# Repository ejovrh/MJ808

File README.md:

# keywords:

Magicshine, bicycle front light, MJ808, MJ-808, MJ818, MJ-818, bicycle rear light, CAN bus

BRANCH GW

# 0. this all is still under heavy development
front and rear lamps do work together and can be used on a bike.
logic unit and auxiliary devices are still WIP.

# 1. abstract:
this undertaking originated as an attempt to redesign the MJ808/MJ818 lights by:
- designing a custom PCB w. driver/controller ICs,
- writing firmware for a stm32 microcontroller,
- encapsulating the above in MJ808's/MJ818's original housing,
- combining:
 - the rear light (MJ818), 
 - the front light (MJ808) and 
 - a control unit into an interconnected smart bicycle light system.
 - developing further auxiliary devices which extend functionality of the lights.

# 2. light system topology (in ascii art)
**==** and **||** denote the CAN bus, power lines are omitted.

## 2.1 - current working setup
front and rear lights are interconnected via the CAN bus; the front light activates the rear light via commands transmitted over CAN.

	(front light) - (rear light)
	------------------------------------------------
	(mj808) ======  (mj818)
	
## 2.2 - WIP setup
front and rear lights are extended in their functionality by other auxiliary devices interconnected via the CAN bus
	
	(front light) - (control unit) - (rear light)
	------------------------------------------------
	(mj808) ====== (control unit)  ====== (mj818)
                      ||		||
                      ||		||		
                      ||	(future device(s))
                    (dynamo)

# 3. description of the original light
google [magicshine mj-818](https://www.google.com/search?q=magicshine+mj-818) / [magicshine mj-808](https://www.google.com/search?q=magicshine+mj-808) for an idea what the lights are and look like.
	
these are decent made-in-china bicycle lights operated off a 2S2P Li-Lion battery pack.

their functionality, apart from producing light, sucks.

# 4. motivation for development
light operating mode selection and high power consumption on the original lights is what i would like to have different.
	
the only reasonable way to achieve this is to start from scratch.

# 5. required software for DIY building
- eagle for PCB layout & schematics,
- STM32CubeIDE for the code,
- one STLink or similar,
- some cheapo arduino/stm-based CAN capable dev. board for quick and dirty CAN testing
- SMD soldering equipment and skills,
- parts.

# 6. repo structure
- /datasheets/*/: contains what the name suggests,
- /dwg/: AutoCAD drawings & STLs of various sub-components,
- /eagle designs/: contains subfolders with eagle designs (.brd, .sch & BOMs) of various sub-components:
	- mj808/: the front light,
	- mj818/: the rear light,
	- mj828/: a small handlebar mounted UI (nothing fancy), WIP,
	- mj838/ (aka. Čos): a dynamo thing, WIP,
	- mjfoo/: a development board based on the mj8x8 infractructure,
	- branch-dependant: whatever stuff is in the particular branch.
- /mj8x8/: C source code for everything, to be used with STM32CubeIDE
- /saleae/: HLA for the logic analyzer
	
# 7. hardware
look in [/datasheets/](https://github.com/ejovrh/MJ808/tree/master/datasheets) for a BOM.

core components:
- 4-layer PCB manufactured via [OSH Park](https://oshpark.com/),
- [STM32F042G6U6](https://www.st.com/en/microcontrollers-microprocessors/stm32f042g6.html) microcontroller, 
- [TCAN334](https://www.ti.com/product/TCAN334) 3.3V CAN transciever,
- [MAX16819](https://www.maximintegrated.com/en/products/power/led-drivers/MAX16819.html) & [MAX16820](https://www.maximintegrated.com/en/products/power/led-drivers/MAX16820.html) LED drivers,
- [LDK320](https://www.st.com/en/power-management/ldk320.html) 5V LDO,
- 0402 passives and
- Cree [XM-L](https://www.cree.com/led-components/products/xlamp-leds-discrete/xlamp-xm-l) and [XP-E](https://www.cree.com/led-components/products/xlamp-leds-discrete/xlamp-xp-e) high power LEDs.

when chosing components the primary criterium was size, since everything needed to fit into existing housings.
maximizing light output to the extreme was not a design factor.

# 8. software
## 8.1 general overview
the language of choice is C, written in an object-oriented fashion:
- it uses HAL. (don't like it?  -> go away.),
- common core components translate into an [abstract base class](https://github.com/ejovrh/MJ808/tree/master/MJ808/MJ808/mj8x8) (implemented via C-structs), 
- concrete implementations (e.g. [mj808](https://github.com/ejovrh/MJ808/tree/master/MJ808/MJ808/mj808) ) translate into derived classes (again C-structs),
- methods are generally implemented via function pointers ([e.g. CAN driver message operations](https://github.com/ejovrh/MJ808/blob/master/MJ808/MJ808/mj8x8/mcp2515.h)),
- behaviour is sometimes achieved with [OO interfaces](https://github.com/ejovrh/MJ808/tree/master/MJ808/MJ808/led), 
- polymorphism is implemented manually via constructors ([ctor in mj808_t](https://github.com/ejovrh/MJ808/blob/master/MJ808/MJ808/mj808/mj808.c)) and
- information is hidden by nesting C-structs and placing them into either [.c](https://github.com/ejovrh/MJ808/blob/master/MJ808/MJ808/mj808/mj808.c) or [.h](https://github.com/ejovrh/MJ808/blob/master/MJ808/MJ808/mj808/mj808.h) files.

due to memory limitations there are only hints of SOLID and design patterns to be found.

code is commented in a somewhat reasonable manner.

## 8.2 detailed description
TODO

## 8.2.1 mj808 - front light

## 8.2.2 mj818 - rear light

## 8.2.3 mj828 - UI

## 8.2.4 mjfoo - development board

## 8.2.5 mj838 - power controller

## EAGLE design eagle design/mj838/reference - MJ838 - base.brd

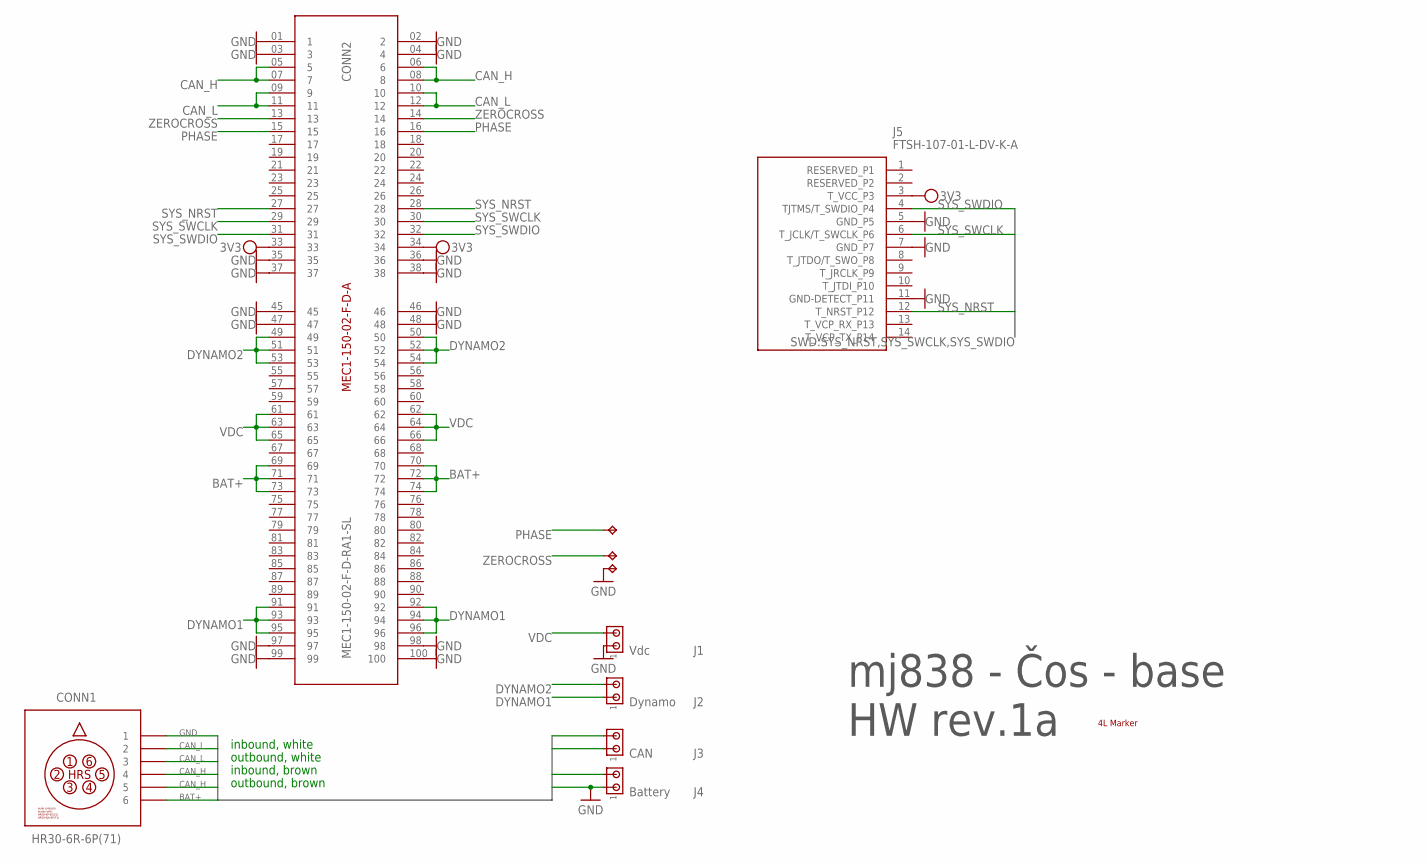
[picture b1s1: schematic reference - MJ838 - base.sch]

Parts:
CONN2: MEC1-150-02-F-D-RA1-SL; SAMTEC_MEC1-150-2-F-D-RA1
J1: Vdc; 10X02MTA
J2: Dynamo; 10X02MTA
J3: CAN; 10X02MTA
J4: Battery; 10X02MTA
J5: FTSH-107-01-L-DV-K-A; FTSH10701LDVKA
MARKER2: 4 Layer marker; 4L
TP1, TP2, TP3: TPPAD1-13; P1-13

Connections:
3V3: CONN2.33, CONN2.34, J5.3 (T_VCC_P3)
BAT+: CONN2.69, CONN2.70, CONN2.71, CONN2.72, CONN2.73, CONN2.74, J4.2
CAN_H: CONN2.05 (5), CONN2.06 (6), CONN2.07 (7), CONN2.08 (8), J3.2
CAN_L: CONN2.09 (9), CONN2.10, CONN2.11, CONN2.12, J3.1
DYNAMO1: CONN2.91, CONN2.92, CONN2.93, CONN2.94, CONN2.95, CONN2.96, J2.1
DYNAMO2: CONN2.49, CONN2.50, CONN2.51, CONN2.52, CONN2.53, CONN2.54, J2.2
GND: CONN2.01 (1), CONN2.02 (2), CONN2.03 (3), CONN2.04 (4), CONN2.35, CONN2.36, CONN2.37, CONN2.38, CONN2.45, CONN2.46, CONN2.47, CONN2.48, CONN2.97, CONN2.98, CONN2.99, CONN2.100, J1.1, J4.1, J5.5 (GND_P5), J5.7 (GND_P7), J5.11 (GND-DETECT_P11), TP1.TP
PHASE: CONN2.15, CONN2.16, TP3.TP
SYS_NRST: CONN2.27, CONN2.28, J5.12 (T_NRST_P12)
SYS_SWCLK: CONN2.29, CONN2.30, J5.6 (T_JCLK/T_SWCLK_P6)
SYS_SWDIO: CONN2.31, CONN2.32, J5.4 (TJTMS/T_SWDIO_P4)
VDC: CONN2.61, CONN2.62, CONN2.63, CONN2.64, CONN2.65, CONN2.66, J1.2
ZEROCROSS: CONN2.13, CONN2.14, TP2.TP

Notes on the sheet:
inbound, white
inbound, brown
outbound, white
outbound, brown
mj838 - Čos - base HW rev.1a

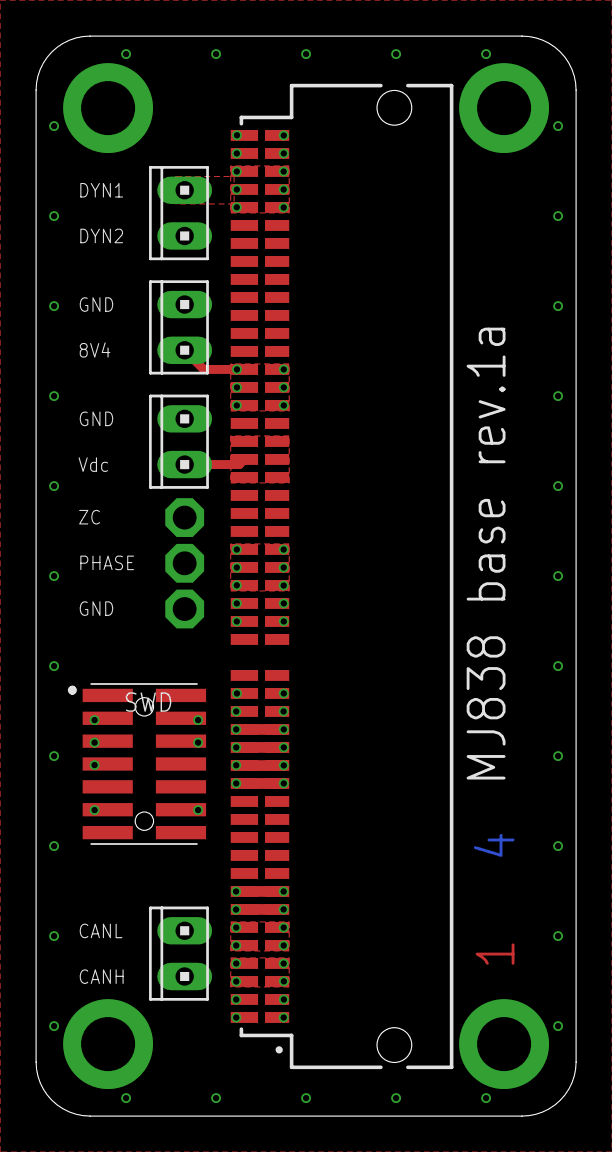
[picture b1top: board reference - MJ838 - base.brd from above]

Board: 4 copper layers, 30.0 x 60.0 mm, 10 parts (0 on the bottom side), 13 nets.

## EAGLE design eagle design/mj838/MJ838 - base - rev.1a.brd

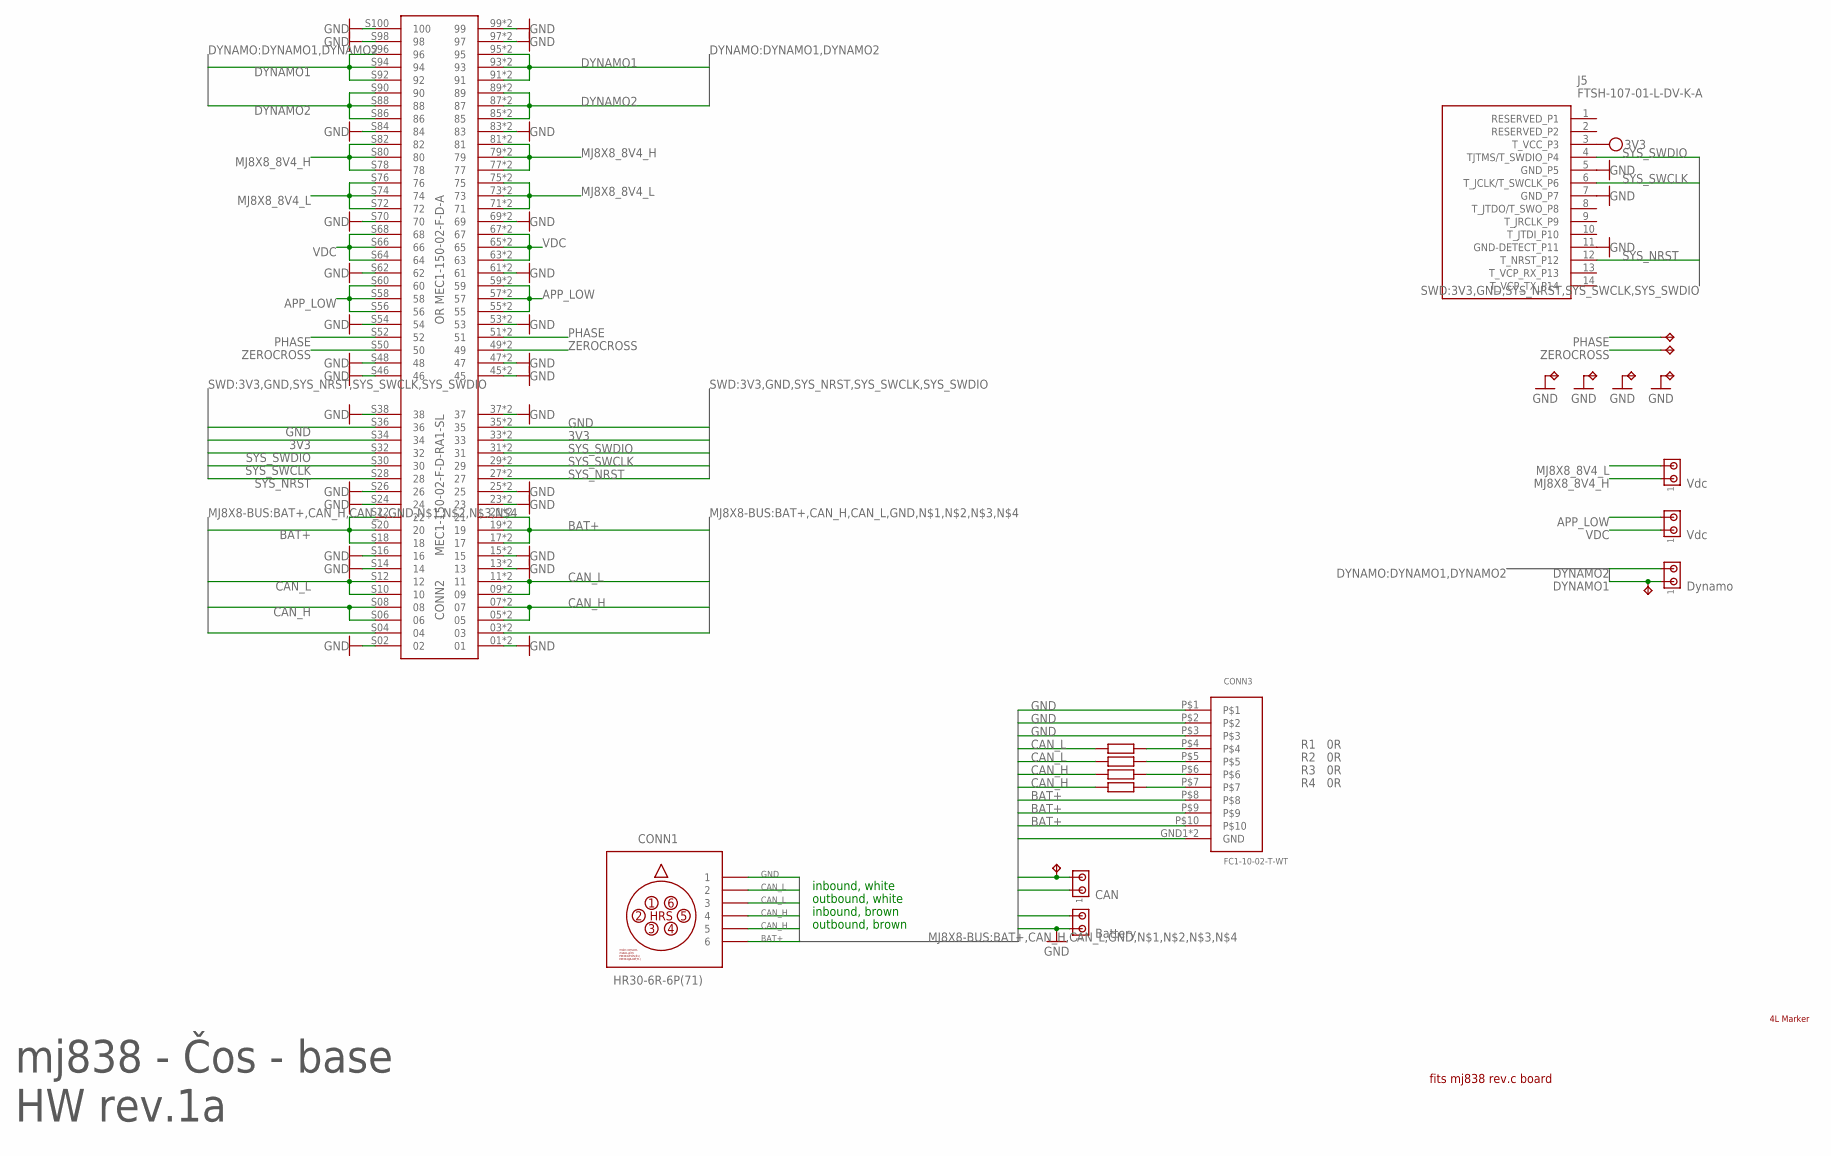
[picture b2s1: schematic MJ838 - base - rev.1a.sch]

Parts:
CONN2: MEC1-150-02-F-D-RA1-SL; MEC1-150-02-F-D-COMBINED
CONN3: FC1-10-02-T-WT; SMD
J2: Dynamo; 10X02MTA
J3: CAN; 10X02MTA
J4: Battery; 10X02MTA
J5: FTSH-107-01-L-DV-K-A; FTSH10701LDVKA
J6, J7: Vdc; 10X02MTA
MARKER2: 4 Layer marker; 4L
R1, R2, R3, R4: 0R; R0402
TP1, TP2, TP3, TP4, TP5, TP6, TP8, TP9: TPPAD1-13; P1-13

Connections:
3V3: CONN2.33, CONN2.R33 (33), CONN2.S34 (34), J5.3 (T_VCC_P3)
APP_LOW: CONN2.55, CONN2.57, CONN2.59, CONN2.R55 (55), CONN2.R57 (57), CONN2.R59 (59), CONN2.S56 (56), CONN2.S58 (58), CONN2.S60 (60), J7.2
BAT+: CONN2.17, CONN2.19, CONN2.21, CONN2.R17 (17), CONN2.R19 (19), CONN2.R21 (21), CONN2.S18 (18), CONN2.S20 (20), CONN2.S22 (22), CONN3.P$8, CONN3.P$9, CONN3.P$10, J4.2
CAN_H: CONN2.05, CONN2.07, CONN2.R05 (05), CONN2.R07 (07), CONN2.S06 (06), CONN2.S08 (08), J3.2, R3.1, R4.1, TP6.TP
CAN_L: CONN2.09, CONN2.11, CONN2.R09 (09), CONN2.R11 (11), CONN2.S10 (10), CONN2.S12 (12), J3.1, R1.1, R2.1
DYNAMO1: CONN2.91, CONN2.93, CONN2.95, CONN2.R91 (91), CONN2.R93 (93), CONN2.R95 (95), CONN2.S92 (92), CONN2.S94 (94), CONN2.S96 (96), J2.1, TP5.TP
DYNAMO2: CONN2.85, CONN2.87, CONN2.89, CONN2.R85 (85), CONN2.R87 (87), CONN2.R89 (89), CONN2.S86 (86), CONN2.S88 (88), CONN2.S90 (90), J2.2
GND: CONN2.01, CONN2.03, CONN2.13, CONN2.15, CONN2.23, CONN2.25, CONN2.35, CONN2.37, CONN2.45, CONN2.47, CONN2.53, CONN2.61, CONN2.69, CONN2.83, CONN2.97, CONN2.99, CONN2.R01 (01), CONN2.R03 (03), CONN2.R13 (13), CONN2.R15 (15), CONN2.R23 (23), CONN2.R25 (25), CONN2.R35 (35), CONN2.R37 (37), CONN2.R45 (45), CONN2.R47 (47), CONN2.R53 (53), CONN2.R61 (61), CONN2.R69 (69), CONN2.R83 (83), CONN2.R97 (97), CONN2.R99 (99), CONN2.S02 (02), CONN2.S04 (04), CONN2.S14 (14), CONN2.S16 (16), CONN2.S24 (24), CONN2.S26 (26), CONN2.S36 (36), CONN2.S38 (38), CONN2.S46 (46), CONN2.S48 (48), CONN2.S54 (54), CONN2.S62 (62), CONN2.S70 (70), CONN2.S84 (84), CONN2.S98 (98), CONN2.S100 (100), CONN3.GND1 (GND), CONN3.GND2 (GND), CONN3.P$1, CONN3.P$2, CONN3.P$3, J4.1, J5.5 (GND_P5), J5.7 (GND_P7), J5.11 (GND-DETECT_P11), TP1.TP, TP4.TP, TP8.TP, TP9.TP
MJ8X8_8V4_H: CONN2.77, CONN2.79, CONN2.81, CONN2.R77 (77), CONN2.R79 (79), CONN2.R81 (81), CONN2.S78 (78), CONN2.S80 (80), CONN2.S82 (82), J6.1
MJ8X8_8V4_L: CONN2.71, CONN2.73, CONN2.75, CONN2.R71 (71), CONN2.R73 (73), CONN2.R75 (75), CONN2.S72 (72), CONN2.S74 (74), CONN2.S76 (76), J6.2
unnamed: CONN3.P$4, R1.2
unnamed: CONN3.P$5, R2.2
unnamed: CONN3.P$6, R3.2
unnamed: CONN3.P$7, R4.2
PHASE: CONN2.51, CONN2.R51 (51), CONN2.S52 (52), TP3.TP
SYS_NRST: CONN2.27, CONN2.R27 (27), CONN2.S28 (28), J5.12 (T_NRST_P12)
SYS_SWCLK: CONN2.29, CONN2.R29 (29), CONN2.S30 (30), J5.6 (T_JCLK/T_SWCLK_P6)
SYS_SWDIO: CONN2.31, CONN2.R31 (31), CONN2.S32 (32), J5.4 (TJTMS/T_SWDIO_P4)
VDC: CONN2.63, CONN2.65, CONN2.67, CONN2.R63 (63), CONN2.R65 (65), CONN2.R67 (67), CONN2.S64 (64), CONN2.S66 (66), CONN2.S68 (68), J7.1
ZEROCROSS: CONN2.49, CONN2.R49 (49), CONN2.S50 (50), TP2.TP

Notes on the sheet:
inbound, white
inbound, brown
outbound, white
outbound, brown
mj838 - Čos - base HW rev.1a
fits mj838 rev.c board
OR MEC1-150-02-F-D-A

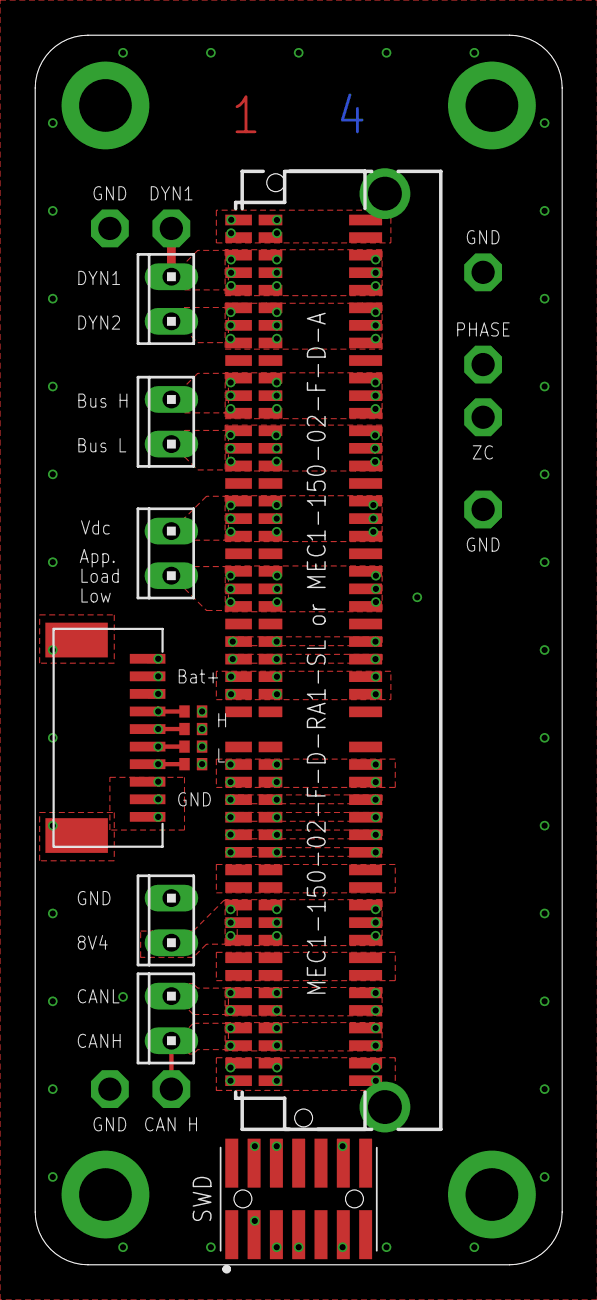
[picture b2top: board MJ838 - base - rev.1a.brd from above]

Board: 4 copper layers, 30.0 x 70.0 mm, 21 parts (0 on the bottom side), 20 nets.

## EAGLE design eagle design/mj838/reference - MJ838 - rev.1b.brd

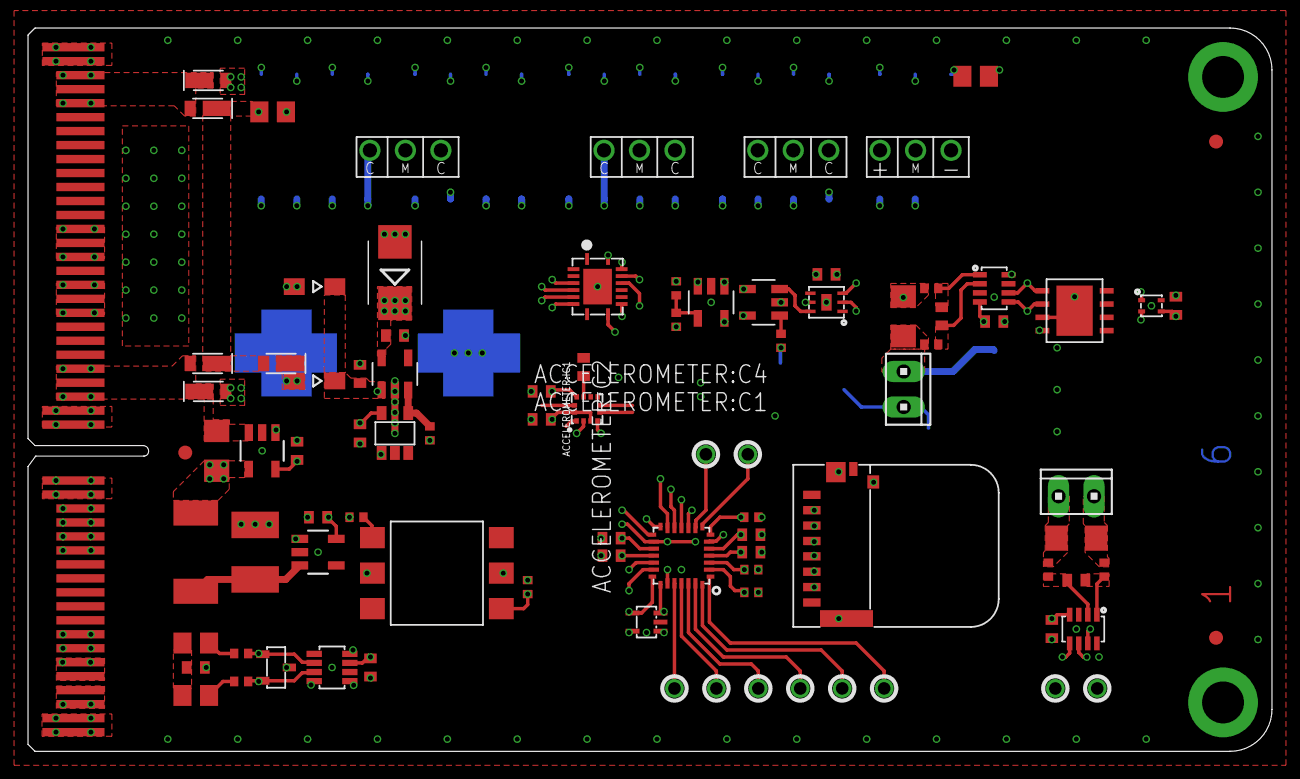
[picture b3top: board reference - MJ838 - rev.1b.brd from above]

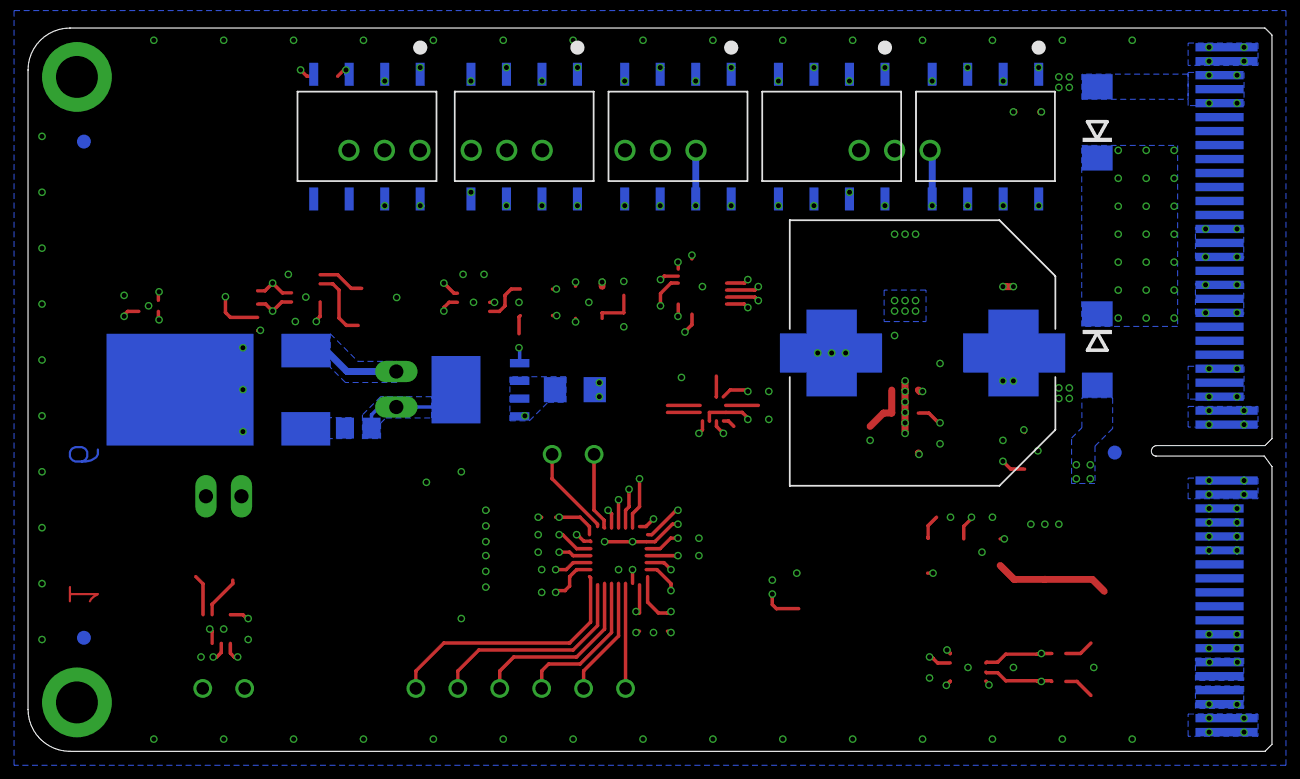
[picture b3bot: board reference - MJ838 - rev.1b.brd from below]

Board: 6 copper layers, 89.0 x 51.8 mm, 107 parts (16 on the bottom side), 76 nets.

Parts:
12R_OHMIC_LOAD:C1: 0.1uF / 10V; C0402
12R_OHMIC_LOAD:IC1: DAC121C081CISD/NOPB; WSON-6
12R_OHMIC_LOAD:IC2, 12R_OHMIC_LOAD:IC4: AD8515ARTZ-REEL7; SOT-23-5
12R_OHMIC_LOAD:IC3: PH2925U,115; SOT669
12R_OHMIC_LOAD:J3: Application; 10X02MTA
12R_OHMIC_LOAD:R1: 3k; R0402
12R_OHMIC_LOAD:R2: 0.1R / 0.5W - LVK12R100CER; R1206
12R_OHMIC_LOAD:R3: 1k; R0402
12R_OHMIC_LOAD:R4: 27k; R0402
12R_OHMIC_LOAD:R5: 12R, 20W, AP725 12R F; TO-263-2
12R_OHMIC_LOAD:R6: 0; R0805
ACCELEROMETER:C1: 0.1uF / 10V; C0402
ACCELEROMETER:C2: 0.2uF / 10V; C0402
ACCELEROMETER:C4: 0.11uF / 10V; C0402
ACCELEROMETER:IC1: ADXL367BCCZ-RL7; LGA-12
CAN_INFRA:C1: 47nF / 10V; C0402
CAN_INFRA:C5: 0.1uF / 10V; C0402
CAN_INFRA:IC1: TCAN334GDCNT; SOT23-8
CAN_INFRA:IC2: SZNUP2105LT1G; SOT-23-3
CAN_INFRA:R1, CAN_INFRA:R2: 60R, 0.5W; R0805
CAN_INFRA:R3, CAN_INFRA:R4: 0; R0402
CONN1: MEC1-150-02-F-D-RA1-SL; SMD
D1: SMLVT3V3; SMB
FE-RAM:IC1: FM24CL64B-DGTR; DFN8
FID1, FID2, FID3, FID4, FID5, FID6: n/a; FIDUCIAL_1MM
HUMIDITY_SENSOR:C5: 0.1uF / 10V; C0402
HUMIDITY_SENSOR:IC1: SHT40-AD1F-R2; SMD
IC1: ESDALC6V1W5; SOT323-5
INA1:C1, INA219:C1: 0.1uF / 10V; C0402
INA1:C2, INA219:C2: ???; C0402
INA1:IC3, INA219:IC3: INA219BIDCNT; SOT-23-8
INA1:R3, INA1:R5, INA219:R3, INA219:R5: ???; R0402
INA1:R4, INA219:R4: 0.1R / 0.5W - LVK12R100CER; R1206
J1: sense 1; 10X02MTA
MARKER1: 6 layer; 6L
RECTIFIER:3V3:C1, RECTIFIER:3V3:C2, RECTIFIER:3V3:C7: 1uF / 10V; C0402
RECTIFIER:3V3:IC1: R3119N058A; SOT23-5
RECTIFIER:3V3:IC2: LDK320AM33R; SOT-23-5L
RECTIFIER:3V3:R1: 100k / 0.1W; R0402
RECTIFIER:D1, RECTIFIER:D2: BAT 60A E6327; SOD323-W
RECTIFIER:GRAETZ+DELON:D1, RECTIFIER:GRAETZ+DELON:D2, RECTIFIER:GRAETZ+DELON:D3, RECTIFIER:GRAETZ+DELON:D4: CUHS20S30,H3F; US2H
RECTIFIER:GRAETZ+DELON:DELON:C1: 330μF / 35V / ultralow ESR; TH-2S
RECTIFIER:GRAETZ+DELON:DELON:SSR_NO/NO3:IC1: LAA710S; SMD_DIP8
RECTIFIER:GRAETZ+DELON:IC1: TLC59208FIRGYR; VQFN16
RECTIFIER:GRAETZ+DELON:R1: 625; R0805
RECTIFIER:GRAETZ+DELON:TUNING_CAPS:C2, RECTIFIER:GRAETZ+DELON:TUNING_CAPS:C3, RECTIFIER:GRAETZ+DELON:TUNING_CAPS:C4: 1500μF / 35V / ultralow ESR; TH-2S-BACK-TO-BACK
RECTIFIER:GRAETZ+DELON:TUNING_CAPS:R2: 47k; R0805
RECTIFIER:GRAETZ+DELON:TUNING_CAPS:SSR_NO/NO1:IC1, RECTIFIER:GRAETZ+DELON:TUNING_CAPS:SSR_NO/NO2:IC1, RECTIFIER:GRAETZ+DELON:TUNING_CAPS:SSR_NO/NO3:IC1, RECTIFIER:GRAETZ+DELON:TUNING_CAPS:SSR_NO/NO4:IC1: LAA710S; SMD_DIP8
RECTIFIER:OVP:D1, RECTIFIER:OVP:D2: 19V/5W; DO214AA
RECTIFIER:PHASE_SHIFT:C1: 0.1uF / 10V; C0402
RECTIFIER:PHASE_SHIFT:IC1: LT1716CS5#TRMPBF; SOT23-5
RECTIFIER:PHASE_SHIFT:R4: 0.01R / 0.5W / 0.25%; R1206
RECTIFIER:SMOOTHING_CAP:C1: EEE-FK1E472SV; CAP_EEEFK1E472SV
RECTIFIER:SMOOTHING_CAP:D8: CUHS20S30,H3F; US2H
RECTIFIER:ZERO-CROSS_DETECTOR:C3: 0.1uF / 10V; C0402
RECTIFIER:ZERO-CROSS_DETECTOR:C8: 10nF / 100v; C1812
RECTIFIER:ZERO-CROSS_DETECTOR:IC1: 4N25-X009T; SMD-6
RECTIFIER:ZERO-CROSS_DETECTOR:IC3: LT1716CS5#TRMPBF; SOT23-5
RECTIFIER:ZERO-CROSS_DETECTOR:R1: 10k/3W; R2512
RECTIFIER:ZERO-CROSS_DETECTOR:R2: 100R; R0402
RECTIFIER:ZERO-CROSS_DETECTOR:R3: 10k; R0402
SD_CARD:IC2: 47309-2651; MICRO_SD_CONNECTOR
SD_CARD:R1: 10k; R0402
STM32F04:C1, STM32F04:C5, STM32F04:C7: 0.1uF / 10V; C0402
STM32F04:C4: 1uF / 10V; C0402
STM32F04:IC2: STM32F042G6U6; UFQFPN-28
STM32F04:R1, STM32F04:R2: 1k; R0402
TP1, TP2, TP3, TP4, TP5, TP6, TP7, TP8, TP9, TP10: CAN high; TH-0.9

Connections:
2IN+: INA1:R4.1, INA1:R5.2, J1.1
2IN-: INA1:R3.2, INA1:R4.2, J1.2
3V3: 12R_OHMIC_LOAD:C1.2, 12R_OHMIC_LOAD:IC1.5, 12R_OHMIC_LOAD:IC2.5, 12R_OHMIC_LOAD:IC4.5, ACCELEROMETER:C1.2, ACCELEROMETER:C4.2, ACCELEROMETER:IC1.3_MISO/ASEL, ACCELEROMETER:IC1.10_VS, ACCELEROMETER:IC1.12_VDDIO, CAN_INFRA:C5.1, CAN_INFRA:IC1.P$3, CONN1.33, CONN1.34, D1.C, FE-RAM:IC1.8, HUMIDITY_SENSOR:C5.1, HUMIDITY_SENSOR:IC1.VDD, INA1:C1.1, INA1:IC3.P$4, INA1:IC3.P$7, INA219:C1.1, INA219:IC3.P$4, RECTIFIER:3V3:C7.2, RECTIFIER:3V3:IC2.OUT, RECTIFIER:GRAETZ+DELON:IC1.16, RECTIFIER:GRAETZ+DELON:R1.2, RECTIFIER:PHASE_SHIFT:C1.2, RECTIFIER:PHASE_SHIFT:IC1.5, RECTIFIER:ZERO-CROSS_DETECTOR:C3.2, RECTIFIER:ZERO-CROSS_DETECTOR:IC1.5, RECTIFIER:ZERO-CROSS_DETECTOR:IC3.5, RECTIFIER:ZERO-CROSS_DETECTOR:R2.2, SD_CARD:IC2.VDD, SD_CARD:R1.2, STM32F04:C1.2, STM32F04:C4.2, STM32F04:C5.2, STM32F04:IC2.5_VDDA, STM32F04:IC2.17_VDD, STM32F04:IC2.18_VDDIO2, STM32F04:R1.2, STM32F04:R2.2
12R_OHMIC_LOAD:DAC_OUT: 12R_OHMIC_LOAD:IC1.6, 12R_OHMIC_LOAD:IC2.3
12R_OHMIC_LOAD:DRAIN: 12R_OHMIC_LOAD:IC3.D, 12R_OHMIC_LOAD:J3.1, 12R_OHMIC_LOAD:R6.1
12R_OHMIC_LOAD:GATE1: 12R_OHMIC_LOAD:IC3.G, 12R_OHMIC_LOAD:R3.2
12R_OHMIC_LOAD:GATE-DRIVER_OUT: 12R_OHMIC_LOAD:IC2.1, 12R_OHMIC_LOAD:R3.1
12R_OHMIC_LOAD:LOAD_LOW: 12R_OHMIC_LOAD:R5.1, 12R_OHMIC_LOAD:R6.2
12R_OHMIC_LOAD:N$1: 12R_OHMIC_LOAD:IC4.4, 12R_OHMIC_LOAD:R1.2, 12R_OHMIC_LOAD:R4.1
12R_OHMIC_LOAD:VSENSE: 12R_OHMIC_LOAD:IC3.S1, 12R_OHMIC_LOAD:IC3.S2, 12R_OHMIC_LOAD:IC3.S3, 12R_OHMIC_LOAD:IC4.3, 12R_OHMIC_LOAD:R2.2
12R_OHMIC_LOAD:VSENSE-AMP_OUT: 12R_OHMIC_LOAD:IC2.4, 12R_OHMIC_LOAD:IC4.1, 12R_OHMIC_LOAD:R4.2
!LED_RST!: RECTIFIER:GRAETZ+DELON:IC1.13, STM32F04:IC2.6_PA0
!STBY!: CAN_INFRA:IC1.P$8, STM32F04:IC2.23_PA15
ACCELEROMETER:VREG: ACCELEROMETER:C2.2, ACCELEROMETER:IC1.9_VREG_OUT
ADJ_LOAD_HIGH: 12R_OHMIC_LOAD:J3.2, 12R_OHMIC_LOAD:R5.2, INA219:R3.2, INA219:R4.2
BAT+: CONN1.69, CONN1.70, CONN1.71, CONN1.72, CONN1.73, CONN1.74, RECTIFIER:D1.A
CAN_H: CAN_INFRA:IC1.P$7, CAN_INFRA:IC2.2, CAN_INFRA:R3.2, CONN1.5, CONN1.6, CONN1.7, CONN1.8
CAN_INFRA:H: CAN_INFRA:R2.2, CAN_INFRA:R3.1
CAN_INFRA:L: CAN_INFRA:R1.1, CAN_INFRA:R4.1
CAN_INFRA:SPLIT: CAN_INFRA:C1.1, CAN_INFRA:R1.2, CAN_INFRA:R2.1
CAN_L: CAN_INFRA:IC1.P$6, CAN_INFRA:IC2.1, CAN_INFRA:R4.2, CONN1.9, CONN1.10, CONN1.11, CONN1.12
CAN_RX: CAN_INFRA:IC1.P$4, STM32F04:IC2.19_PA9-[PA11]
CAN_TX: CAN_INFRA:IC1.P$1, STM32F04:IC2.20_PA10-[PA12]
CLK: SD_CARD:IC2.CLK, STM32F04:IC2.11_PA5
CS: SD_CARD:IC2.CD/DAT3, STM32F04:IC2.10_PA4
DET: SD_CARD:IC2.DET, SD_CARD:R1.1, STM32F04:IC2.7_PA1
DYNAMO1: CONN1.91, CONN1.92, CONN1.93, CONN1.94, CONN1.95, CONN1.96, RECTIFIER:GRAETZ+DELON:D1.C, RECTIFIER:GRAETZ+DELON:D2.A, RECTIFIER:GRAETZ+DELON:TUNING_CAPS:SSR_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.6_DRAIN2-2, RECTIFIER:GRAETZ+DELON:TUNING_CAPS:SSR_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.8_DRAIN1-2, RECTIFIER:GRAETZ+DELON:TUNING_CAPS:SSR_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.6_DRAIN2-2, RECTIFIER:GRAETZ+DELON:TUNING_CAPS:SSR_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.8_DRAIN1-2, RECTIFIER:OVP:D1.A
DYNAMO2: CONN1.49, CONN1.50, CONN1.51, CONN1.52, CONN1.53, CONN1.54, RECTIFIER:GRAETZ+DELON:D3.C, RECTIFIER:GRAETZ+DELON:D4.A, RECTIFIER:GRAETZ+DELON:TUNING_CAPS:SSR_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.7_DRAIN1-1, RECTIFIER:PHASE_SHIFT:IC1.3, RECTIFIER:PHASE_SHIFT:R4.2
GND: 12R_OHMIC_LOAD:C1.1, 12R_OHMIC_LOAD:IC1.1, 12R_OHMIC_LOAD:IC1.4, 12R_OHMIC_LOAD:IC1.7, 12R_OHMIC_LOAD:IC2.2, 12R_OHMIC_LOAD:IC4.2, 12R_OHMIC_LOAD:R1.1, 12R_OHMIC_LOAD:R2.1, 12R_OHMIC_LOAD:R5.DIE, ACCELEROMETER:C1.1, ACCELEROMETER:C2.1, ACCELEROMETER:C4.1, ACCELEROMETER:IC1.1_SCLK, ACCELEROMETER:IC1.7_GND, ACCELEROMETER:IC1.8_ADC_IN, ACCELEROMETER:IC1.11_GND, CAN_INFRA:C1.2, CAN_INFRA:C5.2, CAN_INFRA:IC1.P$2, CAN_INFRA:IC2.3, CONN1.1, CONN1.2, CONN1.3, CONN1.4, CONN1.35, CONN1.36, CONN1.37, CONN1.38, CONN1.45, CONN1.46, CONN1.47, CONN1.48, CONN1.97, CONN1.98, CONN1.99, CONN1.100, D1.A, FE-RAM:IC1.1, FE-RAM:IC1.2, FE-RAM:IC1.3, FE-RAM:IC1.4, FE-RAM:IC1.7, FE-RAM:IC1.G, HUMIDITY_SENSOR:C5.2, HUMIDITY_SENSOR:IC1.VSS, IC1.GND, INA1:C1.2, INA1:IC3.P$3, INA1:IC3.P$8, INA219:C1.2, INA219:IC3.P$3, INA219:IC3.P$7, INA219:IC3.P$8, RECTIFIER:3V3:C1.2, RECTIFIER:3V3:C2.2, RECTIFIER:3V3:C7.1, RECTIFIER:3V3:IC1.2_GND, RECTIFIER:3V3:IC1.3_GND, RECTIFIER:3V3:IC2.GND, RECTIFIER:GRAETZ+DELON:D2.C, RECTIFIER:GRAETZ+DELON:D4.C, RECTIFIER:GRAETZ+DELON:DELON:C1.3_NEG, RECTIFIER:GRAETZ+DELON:IC1.1, RECTIFIER:GRAETZ+DELON:IC1.2, RECTIFIER:GRAETZ+DELON:IC1.3, RECTIFIER:GRAETZ+DELON:IC1.8, RECTIFIER:GRAETZ+DELON:IC1.17, RECTIFIER:PHASE_SHIFT:C1.1, RECTIFIER:PHASE_SHIFT:IC1.2, RECTIFIER:SMOOTHING_CAP:C1.-, RECTIFIER:ZERO-CROSS_DETECTOR:C3.1, RECTIFIER:ZERO-CROSS_DETECTOR:C8.1, RECTIFIER:ZERO-CROSS_DETECTOR:IC3.2, RECTIFIER:ZERO-CROSS_DETECTOR:IC3.4, RECTIFIER:ZERO-CROSS_DETECTOR:R3.1, SD_CARD:IC2.GND1, SD_CARD:IC2.GND2, SD_CARD:IC2.GND3, SD_CARD:IC2.POL, STM32F04:C1.1, STM32F04:C4.1, STM32F04:C5.1, STM32F04:C7.1, STM32F04:IC2.16_VSS
I2C_SCL: 12R_OHMIC_LOAD:IC1.2, ACCELEROMETER:IC1.4_!CS!/SCL, FE-RAM:IC1.6, HUMIDITY_SENSOR:IC1.SCL, INA1:IC3.P$5, INA219:IC3.P$5, RECTIFIER:GRAETZ+DELON:IC1.14, STM32F04:IC2.3_PF1, STM32F04:R2.1, TP9.P$1
I2C_SDA: 12R_OHMIC_LOAD:IC1.3, ACCELEROMETER:IC1.2_MOSI/SDA, FE-RAM:IC1.5, HUMIDITY_SENSOR:IC1.SDA, INA1:IC3.P$6, INA219:IC3.P$6, RECTIFIER:GRAETZ+DELON:IC1.15, STM32F04:IC2.2_PF0, STM32F04:R1.1, TP10.P$1
INA1:IN+L: INA1:C2.1, INA1:IC3.P$1, INA1:R5.1
INA1:IN-H: INA1:C2.2, INA1:IC3.P$2, INA1:R3.1
INA219:IN+L: INA219:C2.1, INA219:IC3.P$1, INA219:R5.1
INA219:IN-H: INA219:C2.2, INA219:IC3.P$2, INA219:R3.1
LED1: STM32F04:IC2.9_PA3, TP2.P$1
LED2: STM32F04:IC2.8_PA2, TP1.P$1
MISO: SD_CARD:IC2.DAT0, STM32F04:IC2.12_PA6
MOSI: SD_CARD:IC2.CMD, STM32F04:IC2.13_PA7
PB3: STM32F04:IC2.24_PB3, TP3.P$1
PB4: STM32F04:IC2.25_PB4, TP4.P$1
PB5: STM32F04:IC2.26_PB5, TP5.P$1
PB6: STM32F04:IC2.27_PB6, TP6.P$1
PB7: STM32F04:IC2.28_PB7, TP7.P$1
PB8: STM32F04:IC2.1_PB8, TP8.P$1
PHASE: CONN1.15, CONN1.16, RECTIFIER:PHASE_SHIFT:IC1.1, STM32F04:IC2.15_PB1
RECTIFIER:3V3:!EN!: RECTIFIER:3V3:IC1.4_DOUT, RECTIFIER:3V3:IC2.EN, RECTIFIER:3V3:R1.2
RECTIFIER:3V3:CD: RECTIFIER:3V3:C1.1, RECTIFIER:3V3:IC1.5_CD
RECTIFIER:AC: RECTIFIER:OVP:D2.A, RECTIFIER:PHASE_SHIFT:IC1.4, RECTIFIER:PHASE_SHIFT:R4.1, RECTIFIER:ZERO-CROSS_DETECTOR:R1.1
RECTIFIER:GRAETZ+DELON:!SW1!: RECTIFIER:GRAETZ+DELON:IC1.10, RECTIFIER:GRAETZ+DELON:TUNING_CAPS:SSR_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.2_CATHODE1
RECTIFIER:GRAETZ+DELON:!SW2!: RECTIFIER:GRAETZ+DELON:IC1.9, RECTIFIER:GRAETZ+DELON:TUNING_CAPS:SSR_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.2_CATHODE1
RECTIFIER:GRAETZ+DELON:!SW_CA!: RECTIFIER:GRAETZ+DELON:IC1.7, RECTIFIER:GRAETZ+DELON:TUNING_CAPS:SSR_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.4_CATHODE2, RECTIFIER:GRAETZ+DELON:TUNING_CAPS:SSR_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.4_CATHODE2
RECTIFIER:GRAETZ+DELON:!SW_CB!: RECTIFIER:GRAETZ+DELON:IC1.6, RECTIFIER:GRAETZ+DELON:TUNING_CAPS:SSR_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.2_CATHODE1, RECTIFIER:GRAETZ+DELON:TUNING_CAPS:SSR_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.2_CATHODE1
RECTIFIER:GRAETZ+DELON:!SW_CC!: RECTIFIER:GRAETZ+DELON:IC1.5, RECTIFIER:GRAETZ+DELON:TUNING_CAPS:SSR_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.4_CATHODE2, RECTIFIER:GRAETZ+DELON:TUNING_CAPS:SSR_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.4_CATHODE2
RECTIFIER:GRAETZ+DELON:!SW_CD!: RECTIFIER:GRAETZ+DELON:DELON:SSR_NO/NO3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.2_CATHODE1, RECTIFIER:GRAETZ+DELON:IC1.4
RECTIFIER:GRAETZ+DELON:DELON: RECTIFIER:GRAETZ+DELON:DELON:SSR_NO/NO3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.8_DRAIN1-2, RECTIFIER:GRAETZ+DELON:TUNING_CAPS:SSR_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.6_DRAIN2-2, RECTIFIER:GRAETZ+DELON:TUNING_CAPS:SSR_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.8_DRAIN1-2, RECTIFIER:GRAETZ+DELON:TUNING_CAPS:SSR_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.7_DRAIN1-1, RECTIFIER:GRAETZ+DELON:TUNING_CAPS:SSR_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.6_DRAIN2-2, RECTIFIER:GRAETZ+DELON:TUNING_CAPS:SSR_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.8_DRAIN1-2
RECTIFIER:GRAETZ+DELON:DELON:SW1_OUT: RECTIFIER:GRAETZ+DELON:DELON:C1.2_MID, RECTIFIER:GRAETZ+DELON:DELON:SSR_NO/NO3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.7_DRAIN1-1
RECTIFIER:GRAETZ+DELON:SSR_ANODE: RECTIFIER:GRAETZ+DELON:DELON:SSR_NO/NO3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.1_ANODE1, RECTIFIER:GRAETZ+DELON:DELON:SSR_NO/NO3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.3_ANODE2, RECTIFIER:GRAETZ+DELON:R1.1, RECTIFIER:GRAETZ+DELON:TUNING_CAPS:SSR_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.1_ANODE1, RECTIFIER:GRAETZ+DELON:TUNING_CAPS:SSR_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.3_ANODE2, RECTIFIER:GRAETZ+DELON:TUNING_CAPS:SSR_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.1_ANODE1, RECTIFIER:GRAETZ+DELON:TUNING_CAPS:SSR_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.3_ANODE2, RECTIFIER:GRAETZ+DELON:TUNING_CAPS:SSR_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.1_ANODE1, RECTIFIER:GRAETZ+DELON:TUNING_CAPS:SSR_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.3_ANODE2, RECTIFIER:GRAETZ+DELON:TUNING_CAPS:SSR_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.1_ANODE1, RECTIFIER:GRAETZ+DELON:TUNING_CAPS:SSR_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.3_ANODE2
RECTIFIER:GRAETZ+DELON:TUNING_CAPS:CAA: RECTIFIER:GRAETZ+DELON:TUNING_CAPS:C2.1_C, RECTIFIER:GRAETZ+DELON:TUNING_CAPS:SSR_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.5_DRAIN2-1
RECTIFIER:GRAETZ+DELON:TUNING_CAPS:CAB: RECTIFIER:GRAETZ+DELON:TUNING_CAPS:C2.3_C, RECTIFIER:GRAETZ+DELON:TUNING_CAPS:SSR_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.5_DRAIN2-1
RECTIFIER:GRAETZ+DELON:TUNING_CAPS:CBA: RECTIFIER:GRAETZ+DELON:TUNING_CAPS:C3.1_C, RECTIFIER:GRAETZ+DELON:TUNING_CAPS:SSR_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.7_DRAIN1-1
RECTIFIER:GRAETZ+DELON:TUNING_CAPS:CBB: RECTIFIER:GRAETZ+DELON:TUNING_CAPS:C3.3_C, RECTIFIER:GRAETZ+DELON:TUNING_CAPS:SSR_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.7_DRAIN1-1
RECTIFIER:GRAETZ+DELON:TUNING_CAPS:CCA: RECTIFIER:GRAETZ+DELON:TUNING_CAPS:C4.1_C, RECTIFIER:GRAETZ+DELON:TUNING_CAPS:SSR_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.5_DRAIN2-1
RECTIFIER:GRAETZ+DELON:TUNING_CAPS:CCB: RECTIFIER:GRAETZ+DELON:TUNING_CAPS:C4.3_C, RECTIFIER:GRAETZ+DELON:TUNING_CAPS:SSR_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.5_DRAIN2-1
RECTIFIER:GRAETZ+DELON:TUNING_CAPS:TUNING_CAP_BIAS: RECTIFIER:GRAETZ+DELON:TUNING_CAPS:C2.2_MID, RECTIFIER:GRAETZ+DELON:TUNING_CAPS:C3.2_MID, RECTIFIER:GRAETZ+DELON:TUNING_CAPS:C4.2_MID, RECTIFIER:GRAETZ+DELON:TUNING_CAPS:R2.1
RECTIFIER:LDO_IN: RECTIFIER:3V3:C2.1, RECTIFIER:3V3:IC1.1_VDD, RECTIFIER:3V3:IC2.IN, RECTIFIER:3V3:R1.1, RECTIFIER:D1.C, RECTIFIER:D2.C
RECTIFIER:OVP:ZENER_COMMON: RECTIFIER:OVP:D1.C, RECTIFIER:OVP:D2.C
RECTIFIER:SMOOTHINGCAP_IN: RECTIFIER:GRAETZ+DELON:D1.A, RECTIFIER:GRAETZ+DELON:D3.A, RECTIFIER:GRAETZ+DELON:DELON:C1.1_POS, RECTIFIER:GRAETZ+DELON:TUNING_CAPS:R2.2, RECTIFIER:SMOOTHING_CAP:D8.C
RECTIFIER:ZERO-CROSS_DETECTOR:COMPARATOR_OUT: RECTIFIER:ZERO-CROSS_DETECTOR:IC1.2, RECTIFIER:ZERO-CROSS_DETECTOR:IC3.1
RECTIFIER:ZERO-CROSS_DETECTOR:OPAMP_IN-: RECTIFIER:ZERO-CROSS_DETECTOR:C8.2, RECTIFIER:ZERO-CROSS_DETECTOR:IC3.3, RECTIFIER:ZERO-CROSS_DETECTOR:R1.2
RECTIFIER:ZERO-CROSS_DETECTOR:OPTO-ANODE: RECTIFIER:ZERO-CROSS_DETECTOR:IC1.1, RECTIFIER:ZERO-CROSS_DETECTOR:R2.1
SYS_NRST: CONN1.27, CONN1.28, IC1.I1, STM32F04:C7.2, STM32F04:IC2.4_NRST
SYS_SWCLK: CONN1.29, CONN1.30, IC1.I2, STM32F04:IC2.22_PA14
SYS_SWDIO: CONN1.31, CONN1.32, IC1.I3, STM32F04:IC2.21_PA13
VDC: CONN1.61, CONN1.62, CONN1.63, CONN1.64, CONN1.65, CONN1.66, INA219:R4.1, INA219:R5.2, RECTIFIER:D2.A, RECTIFIER:SMOOTHING_CAP:C1.+, RECTIFIER:SMOOTHING_CAP:D8.A
ZEROCROSS: CONN1.13, CONN1.14, IC1.I4, RECTIFIER:ZERO-CROSS_DETECTOR:IC1.4, RECTIFIER:ZERO-CROSS_DETECTOR:R3.2, STM32F04:IC2.14_PB0

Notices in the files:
parts and their libraries:
tag-connect: ©2009 ROFA.cz - modified and updated by Robert Darlington ‹rdarlington@gmail.com›
SparkFun-Coils: Licensing: Creative Commons ShareAlike 4.0 International - https://creativecommons.org/licenses/by-sa/4.0
